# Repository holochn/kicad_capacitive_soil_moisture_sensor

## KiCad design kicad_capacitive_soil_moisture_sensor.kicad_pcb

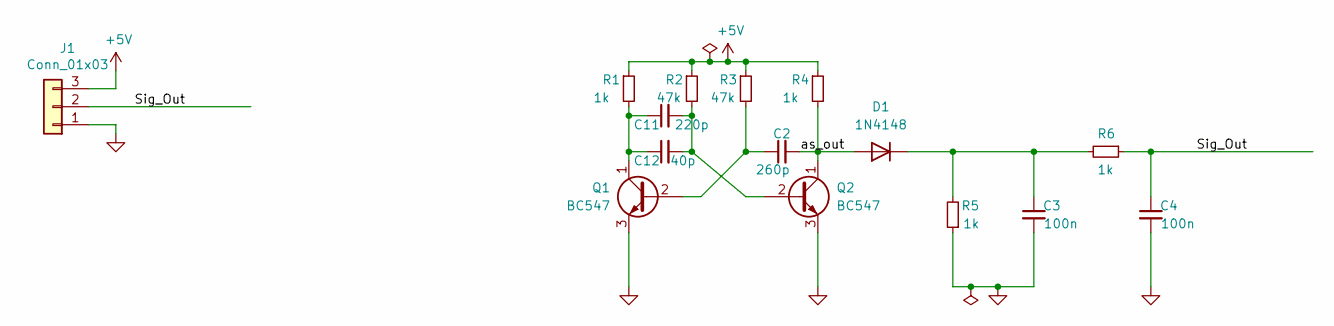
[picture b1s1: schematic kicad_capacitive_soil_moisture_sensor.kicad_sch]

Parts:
C2: 260p; idc_10_finger
C3, C4: 100n; CP_Radial_Tantal_D5.0mm_P2.50mm
C11: 220p; C_Disc_D5.0mm_W2.5mm_P5.00mm
C12: 40p; C_Disc_D5.0mm_W2.5mm_P5.00mm
D1: 1N4148; D_DO-35_SOD27_P7.62mm_Horizontal
J1: Conn_01x03; JST_PH_B3B-PH-K_1x03_P2.00mm_Vertical
Q1, Q2: BC547; TO-92
R1, R4, R5, R6: 1k; R_Axial_DIN0204_L3.6mm_D1.6mm_P5.08mm_Horizontal
R2, R3: 47k; R_Axial_DIN0204_L3.6mm_D1.6mm_P5.08mm_Horizontal

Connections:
+5V: J1.3, R1.1, R2.1, R3.1, R4.1
/Sig_Out: C4.1, J1.2, R6.1
/as_out: C2.2, D1.2 (A), Q2.1 (C), R4.2
GND: C3.2, C4.2, J1.1, Q1.3 (E), Q2.3 (E), R5.1
unnamed: C3.1, D1.1 (K), R5.2, R6.2
unnamed: C2.1, Q1.2 (B), R3.2
unnamed: C11.1, C12.1, Q1.1 (C), R1.2
unnamed: C11.2, C12.2, Q2.2 (B), R2.2

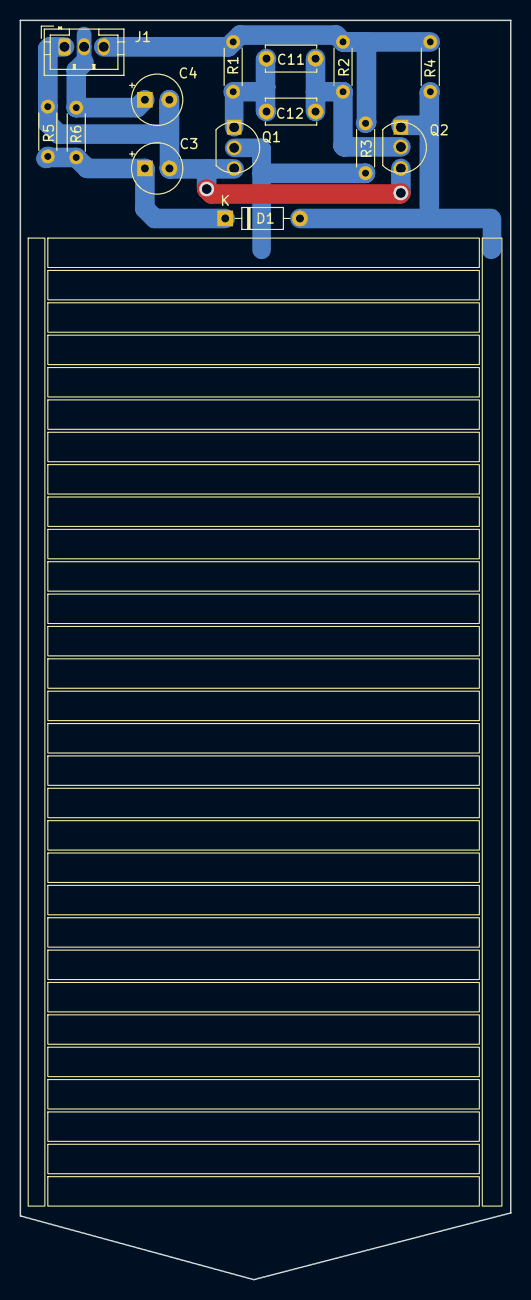
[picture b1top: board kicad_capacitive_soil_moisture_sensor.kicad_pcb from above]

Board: 2 copper layers, 50.0 x 128.4 mm, 15 parts (0 on the bottom side), 8 nets.

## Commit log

2026-04-08 Kicad 7 Version added
2026-04-10 added step export file
